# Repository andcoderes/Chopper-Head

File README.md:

# Chopper Head V2

## Acknowledgments

This firmware was strongly influenced by the [Amidala](https://github.com/thePunderWoman/Amidala) firmware by [thePunderWoman](https://github.com/thePunderWoman).

Firmware for Chopper (C1-1OP) head built on the **ESP32-WROOM-32**. Controls servo animations, RGB LED lighting effects, and communicates wirelessly with a main controller via ESP-NOW.

## Features

- **Servo animations** — Arms, periscope, and greeting motions driven by a Pololu Maestro controller over UART
- **RGB LED effects** — Jewel eyes (7-pixel each), ladder (11-pixel), center eye, and periscope lights with pulsing, bouncing, and color-change animations
- **ESP-NOW communication** — Encrypted peer-to-peer wireless protocol for low-latency remote control
- **Web interface** — Device dashboard, real-time serial monitor, and command sender
- **OTA firmware updates** — Upload new firmware over WiFi through the web interface
- **Unit tests** — Native-platform tests with mock hardware abstractions

## Hardware

| Component | Details |
|---|---|
| Microcontroller | ESP32-WROOM-32 |
| Servo controller | Pololu Maestro (UART2, GPIO 16 TX / GPIO 17 RX) |
| Left jewel eye | NeoPixel, 7 pixels, GPIO 4 |
| Right jewel eye | NeoPixel, 7 pixels, GPIO 18 |
| Center eye | NeoPixel, 1 pixel, GPIO 5 |
| Ladder | NeoPixel, 11 pixels, GPIO 19 |
| Periscope | NeoPixel, 1 pixel, GPIO 2 |

PCB design files are in the `PCB/` directory.

## Project Structure

```
src/
  main.cpp                    Entry point and main loop
  config.h                    Pin definitions, MAC addresses (keys come from secrets.h)
  lights/                     LED control (JewelEye, Ladder, PixelLight, LightController)
  servo/                      Pololu Maestro servo scripts
  communication/              ESP-NOW receiver and message types
  web/                        Embedded web server, logging, serial buffer
include/
  web_pages.h                 Auto-generated embedded HTML (built by scripts/embed_web.py)
  secrets.h                   Auto-generated ESP-NOW keys (built by scripts/load_secrets.py), gitignored
web/                          Web UI source files (HTML, CSS)
test/                         Unit tests and hardware mocks
scripts/
  embed_web.py                Pre-build script that inlines web assets into firmware
  load_secrets.py             Pre-build script: .env -> include/secrets.h
partitions/
  ota_4MB.csv                 OTA partition table
PCB/                          PCB design and CNC routing files
.env.example                  Template for ESP-NOW keys — copy to .env
```

## Prerequisites

- [Visual Studio Code](https://code.visualstudio.com/) with the [PlatformIO IDE](https://platformio.org/install/ide?install=vscode) extension
- Python 3 (used by the `embed_web.py` and `load_secrets.py` build scripts)

## Setup

1. Clone the repository and open it in VS Code.

2. Set up `.env` — see [Generating ESP-NOW keys](#generating-esp-now-keys) below. This covers `PMK_KEY`/`LMK_KEY`, `CONTROLLER_MAC`, and `WIFI_AP_PASSWORD`. The build fails with a clear error if `.env` is missing.

3. Optionally edit `src/config.h`:
   - Change `WIFI_AP_SSID` if desired.

4. Build the firmware:
   ```bash
   pio run -e esp32dev
   ```

5. Upload to the ESP32:
   ```bash
   pio run -e esp32dev -t upload
   ```

6. Open the serial monitor:
   ```bash
   pio device monitor -b 115200
   ```

## Web Interface

Connect to the **ChopperHead** WiFi access point, then open one of:

- `http://chopper.head`
- `http://chopper.local`
- `http://192.168.5.2`

### Pages

| Page | Description |
|---|---|
| Home | Device info — firmware version, MAC address, uptime, heap memory, ESP-NOW status |
| Serial Monitor | Real-time log viewer with command buttons and macro sender |
| Firmware Update | OTA upload with progress tracking |

### API

| Endpoint | Method | Description |
|---|---|---|
| `/api/info` | GET | Device telemetry (JSON) |
| `/api/monitor` | GET | Live log stream (JSON) |
| `/api/command` | POST | Send button or macro commands |

## Controls

### Button Commands (via controller or web)

| Button | Action |
|---|---|
| Y | Toggle arms in/out |
| X | Say hi (both arms) |
| B | Say hi (left arm) |
| D-pad Up | Periscope up |
| D-pad Down | Periscope down |
| D-pad Left/Right | Periscope animation |

### Macros

| Macro ID | Effect |
|---|---|
| 101 | Red eye animation |
| 103 | Periscope up sequence |
| 107 | Custom animation |

## Communication Protocol

The head communicates with the controller using packed structs over ESP-NOW:

**HeadCommand** (controller → head): button presses, macro sequences, volume, idle mode, and connection status.

**HeadTelemetry** (head → controller): connection state, animation status, and uptime. Sent every 1 second.

Connection is considered lost after 5 seconds without data.

## Running Tests

Unit tests run on the native platform (no hardware required):

```bash
pio test -e native
```

Tests cover: LightController, ServoController, ESP-NOW controller, JewelEye, PixelLight, MessageTypes, and startup animation.

## Generating ESP-NOW keys

This board talks to the other Chopper boards over encrypted ESP-NOW. Before
your first build, generate two 16-byte (128-bit) keys — a Primary Master Key
(PMK) and a Local Master Key (LMK) — and put them in a `.env` file
(gitignored, never commit it) at the project root:

```bash
cp .env.example .env
```

Generate two random 16-byte keys, each as 32 hex characters:

```bash
# Option 1: openssl
openssl rand -hex 16   # run twice — once for PMK_KEY, once for LMK_KEY

# Option 2: python
python3 -c "import secrets; print(secrets.token_hex(16))"
```

Edit `.env` and paste the values in:

```
PMK_KEY=<first random hex string>
LMK_KEY=<second random hex string>
```

**These two keys must be byte-for-byte identical across chopper body,
chopper head, and chopper receiver** — generate them once and copy the same
`.env` values into all three projects. Mismatched keys mean the boards can't
decrypt each other's ESP-NOW packets and the mesh will never connect.

`.env` also holds `CONTROLLER_MAC` — the controller's WiFi MAC address (as
hex, e.g. `C0CDD6CA29E0`), which must likewise be identical across all three
firmware projects — and `WIFI_AP_PASSWORD`, the password for this board's
local OTA-update access point (pick your own, at least 8 characters; unlike
the other values, this one doesn't need to match the other boards).

`scripts/load_secrets.py` runs automatically before every build (see
`platformio.ini`) and turns `.env` into `include/secrets.h`, which
`config.h` includes. Neither `.env` nor the generated `secrets.h` are
committed to git.

## License

All rights reserved.

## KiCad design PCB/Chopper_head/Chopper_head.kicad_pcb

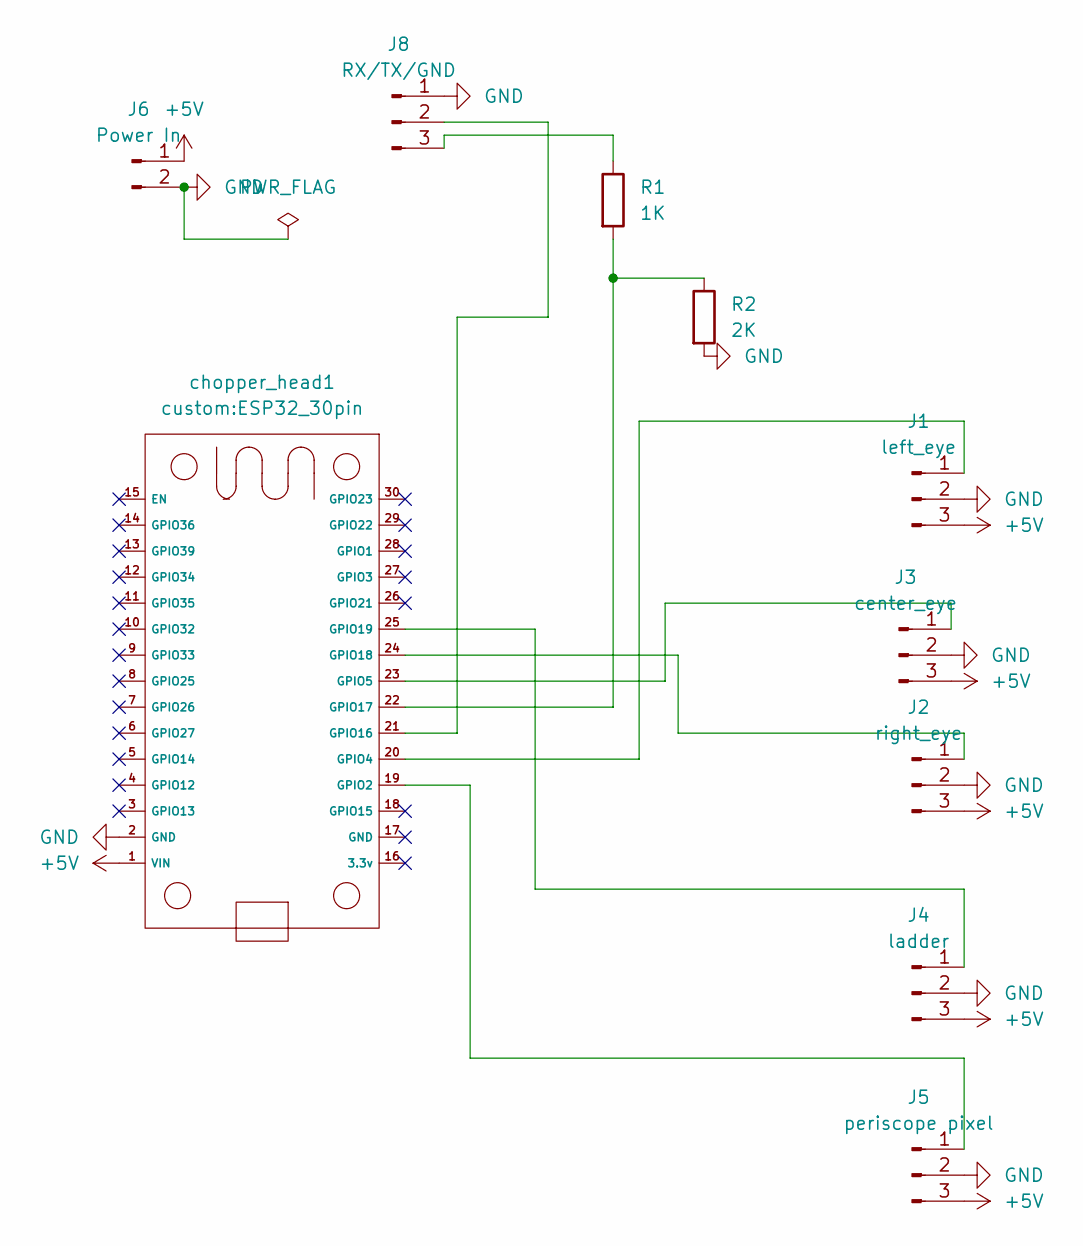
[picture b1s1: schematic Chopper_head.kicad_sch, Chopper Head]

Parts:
J1: left_eye; PinHeader_1x03_P2.54mm_Vertical
J2: right_eye; PinHeader_1x03_P2.54mm_Vertical
J3: center_eye; PinHeader_1x03_P2.54mm_Vertical
J4: ladder; PinHeader_1x03_P2.54mm_Vertical
J5: periscope pixel; PinHeader_1x03_P2.54mm_Vertical
J6: Power In; PinHeader_1x02_P2.54mm_Vertical
J8: RX/TX/GND; PinHeader_1x03_P2.54mm_Vertical
R1: 1K; R_Axial_DIN0204_L3.6mm_D1.6mm_P7.62mm_Horizontal
R2: 2K; R_Axial_DIN0204_L3.6mm_D1.6mm_P7.62mm_Horizontal
chopper_head1: ESP32_30pin

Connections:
+5V: J1.3, J2.3, J3.3, J4.3, J5.3, J6.1, chopper_head1.1 (VIN_1)
GND: J1.2, J2.2, J3.2, J4.2, J5.2, J6.2, J8.1, R2.2, chopper_head1.2 (GND_2), chopper_head1.17 (GND)
unnamed: J1.1, chopper_head1.20 (GPIO4_20)
unnamed: J2.1, chopper_head1.24 (GPIO18_24)
unnamed: J3.1, chopper_head1.23 (GPIO5_23)
unnamed: J4.1, chopper_head1.25 (GPIO19_25)
unnamed: J5.1, chopper_head1.19 (GPIO2_19)
unnamed: J8.2, chopper_head1.21 (GPIO16_21)
unnamed: J8.3, R1.1
unnamed: R1.2, R2.1, chopper_head1.22 (GPIO17_22)

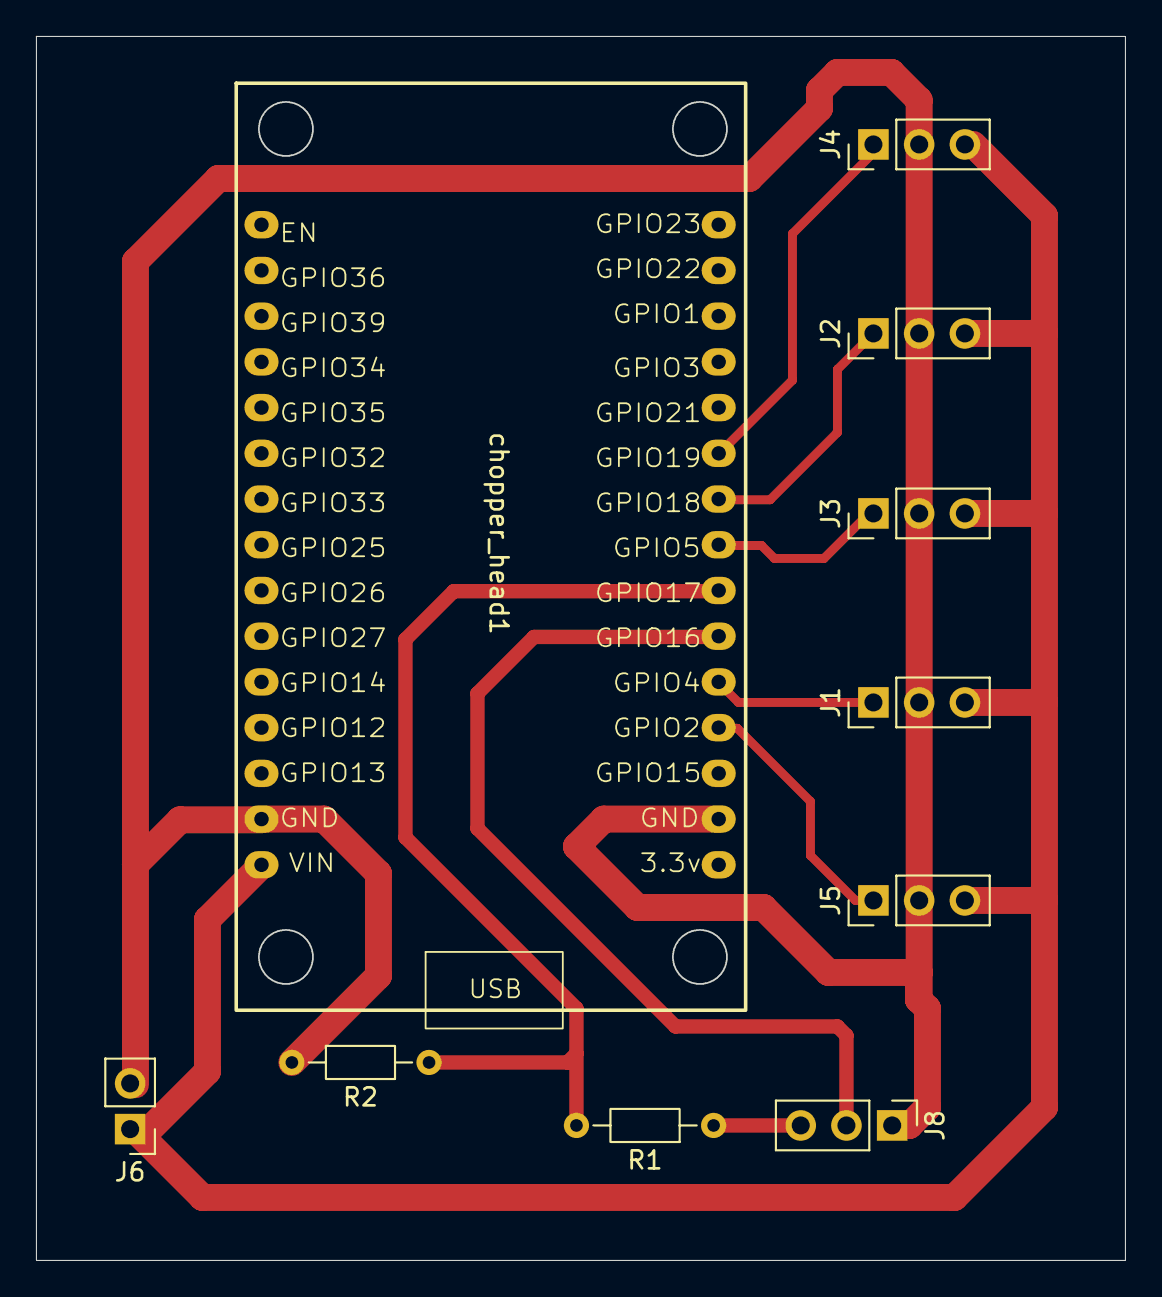
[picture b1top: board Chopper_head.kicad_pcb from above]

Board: 2 copper layers, 60.5 x 68.0 mm, 10 parts (0 on the bottom side), 10 nets.
